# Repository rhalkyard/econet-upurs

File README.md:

# UPURS Dual User Port module for BBC Master Econet Slot

The BBC Master had optional support for Acorn's Econet network. Oddly, all machines had an Econet DIN-5 port populated on the back panel, while the optional hardware to support it was placed on a daughtercard.

This card instead uses the Econet slot to provide a pair of extra user ports, placing a 65C22 VIA at the I/O addresses reserved for the Econet hardware. Additionally, it repurposes the unused Econet port on the back panel for a [UPURS](https://www.retro-kit.co.uk/UPURS/) serial port.

3D rendering of PCB:

Early prototype installed in my BBC Master (excuse the bodge wires, that issue has been resolved)

## Bill of Materials

Reference   | Description
------------|------------
C1          | 0.1 uF ceramic
D1, D2      | 1N4148 (or similar)
J1          | 0.1" pin header, 19x1 pins
J2          | 0.1" pin header, 5x1 pins
J3, J4      | 0.1" pin header, 10x2 pins, shrouded
R1, R2      | 4.7Kohm
U1          | W65C22N VIA, 40 pin DIP

## UPURS

[UPURS](https://www.retro-kit.co.uk/UPURS/) is a fast software-driven RS232 interface, commonly used for exchanging data with modern PCs.

By populating R1, R2, D1 and D2, and bridging JP1 and JP2, the otherwise-unused Econet port can be connected to a serial port for use with UPURS by wiring a cable as follows:

Signal | 180° 5-pin DIN plug  | DE-9 socket
-------|----------------------|-------------
TXD    | 1                    | 3
CTS    | 4                    | 8
Ground | 2                    | 5
RTS    | 5                    | 7
RXD    | 3                    | 2

(note that pins on the DIN plug are numbered as follows, looking at the back of the computer):

```

1           3
   4     5
      2
```

A version of the UPURS software, modified to support this hardware configuration can be found in [this StarDot.co.uk thread](https://stardot.org.uk/forums/viewtopic.php?p=73960&sid=e43f65395b8c5ee131d509cb647cd489#p73960).

## Software Compatibility

In order to use the extra user ports, software must be modified to communicate with the new VIA at `&FEA0` instead of the User VIA at `&FE60`. If only the VIA base address is converted, software will use Port B. To use Port A, software will need to be modified to use `&FEA1` as the port register, and `&FEA3` as the data-direction register. If the synchronous serial port or handshaking functions are to be used with Port A, then further modifications will need to be made.

### Interrupts

The only interrupt line available on the Econet slot is NMI. By default, the VIA's interrupt output is left disconnected, as handling NMIs correctly under MOS is somewhat complicated.

If you want to be able to generate interrupts, bridge jumper J3 to connect the VIA's interrupt output to NMI. Software that wishes to use NMIs must issue appropriate service calls to claim and release the NMI handler area at `&D00`, install their own handler code there, and accept incoming service call requests to release the handler.

### Timing

The Econet slot is clocked off the 'raw' Phi2 CPU clock, rather than the 1MHz clock of the user VIA. This may cause timing complications:

* Reads and writes will occur at 2MHz, which may throw off timing-sensitive bit-banging.

* Timers will count inconsistently - at 2MHz during RAM and ROM accesses, but 1MHz during most I/O accesses.

#### Modifying timing-critical code

From the perspective of the 2MHz clock, access to devices on the 1MHz bus causes the processor to 'lose' two cycles - this is illustrated on Page 443 of the [BBC Microcomputer Advanced User Guide](https://stardot.org.uk/mirrors/www.bbcdocs.com/filebase/essentials/BBC%20Microcomputer%20Advanced%20User%20Guide.pdf). Conveniently, this is the same number of cycles as the `NOP` instruction, so adding either one or two `NOP`s (depending on the instruction) for each time-critical access should be enough to keep timing consistent with a 1MHz VIA.

For absolute addressing, the following rule of thumb applies:

* 4-cycle instructions (`LDA`, `ADC`, `AND`, `ORA` etc.) have 1 memory access, and thus will lose 2 cycles and require one `NOP`.

* 6-cycle instructions (`ASL`, `LSR`, `ROL`, `ROR`, `INC`, `DEC`) have two memory accesses, and thus will lose 4 cycles and require two `NOP`s.

In general, putting the `NOP`(s) before the instruction in question should provide the closest approximation to the 1MHz timing, but that may vary based on

## Econet Slot Information

If you want to build your own hardware to fit the Master's Econet slot, this information might be of use:

The Econet slot provides 16 addresses from `&FEA0`-`&FEAF`, accessed at the full 2MHz CPU speed. The `/NMI` interrupt line is exposed as `/NETINT` and suitable for either TTL or open-collctor outputs, but `/IRQ` is not available.

### Pinouts

#### SK5 (Econet Module bus connector)

SK5 is a 1x19 socket with 0.1" pin spacings, suitable for regular square-pin headers.

For some reason, the pins are numbered A, B, 1..17, instead of 1..19.

Pins are numbered from left to right, when viewing the computer from the front.

Pin   | Signal
------|-------
A     | A3
B     | A2
1     | /NETINT (gets ORed into /NMI by IC15)
2     | R/W
3     | /ADLC (select line for addresses `&FEA0`-`&FEAF`, generated by IC15)
4     | Phi2 (2 MHz clock)
5     | A0
6     | A1
7-14  | D0-D7
15    | /RESET
16    | 0V
17    | +5V

Note that the Econet slot is not on the 1MHz bus - Phi2 is the 'raw' CPU clock, connected to the same net as the processor. As well as the faster access speed, this also means that the clock will be stretched to 1MHz during 1MHz bus accesses. This will cause issues with devices that derive internal clocks from their system-clock input (such as the timers on a VIA).

`/NETINT` goes directly to the IC15 I/O controller (i.e. no wired-OR connections), and has a 2.2K pull-up resistor. This should make it suitable for either open-collector or TTL IRQ outputs.

#### SK6 (Econet module port connector)

SK6 is a 1x5 socket with 0.1" pin spacings, suitable for standard square-pin headers. It connects to the Econet port on the rear of the machine, as follows.

SK6   | Econet port
------|------------
1     | 1
2     | 4
3     | 2 (grounded on main board)
4     | 5
5     | 3

Some machines (non-UK market boards?) may have a common-mode choke array (SIL2) between SK6 and the Econet port.

### Dimensions

Measurement annotations have been added to the PCB layout file in the 'User.Comments' layer.

There is ample space to extend the circuit board to the left, however, space is constrained on all other sides - case edges to the right and rear, and ROM sockets toward the front.

## References

* [StarDot thread on adding an 'Econet User Port'](https://stardot.org.uk/forums/viewtopic.php?f=3&t=7149)

* [Redrawn BBC Master schematics](https://stardot.org.uk/forums/viewtopic.php?t=22660)

* [BBC Master Advanced Reference Manual](https://stardot.org.uk/forums/viewtopic.php?t=21734)

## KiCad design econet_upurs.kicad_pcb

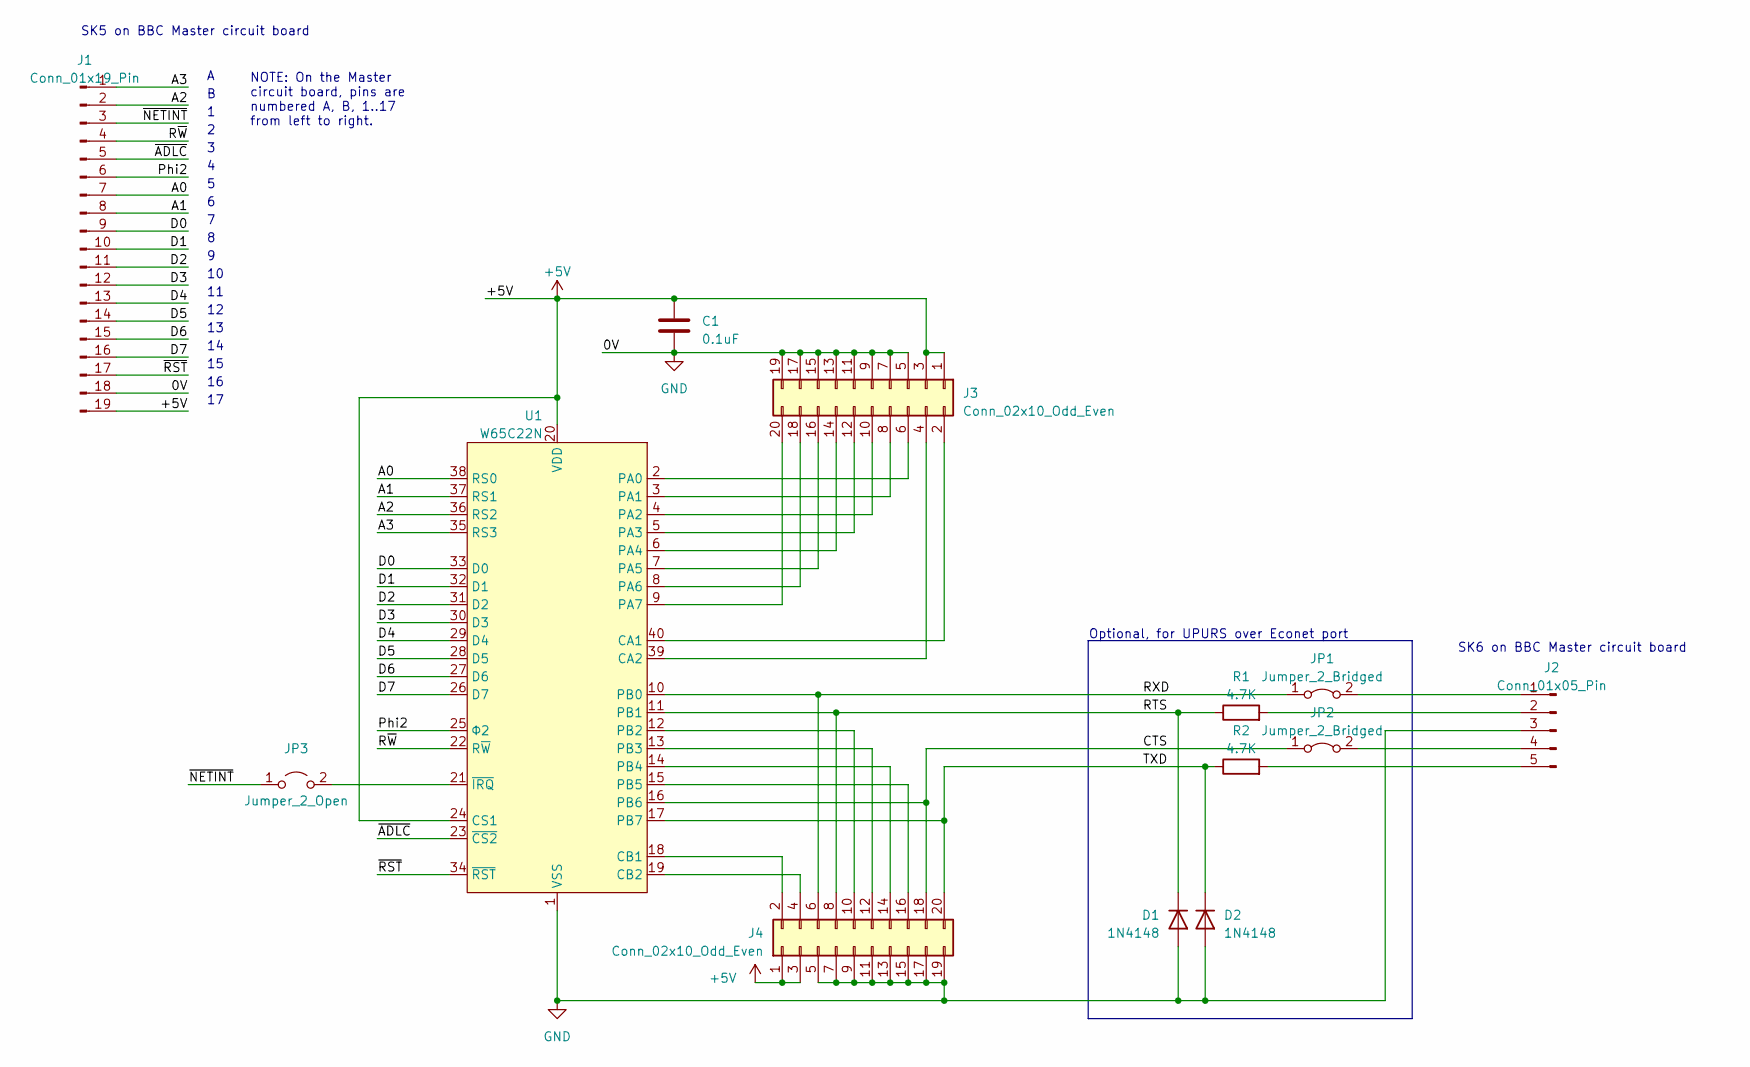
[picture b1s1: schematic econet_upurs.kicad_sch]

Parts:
C1: 0.1uF; C_Disc_D3.0mm_W1.6mm_P2.50mm
D1, D2: 1N4148; D_DO-35_SOD27_P7.62mm_Horizontal
J1: Conn_01x19_Pin; PinHeader_1x19_P2.54mm_Vertical
J2: Conn_01x05_Pin; PinHeader_1x05_P2.54mm_Vertical
J3, J4: Conn_02x10_Odd_Even; IDC-Header_2x10_P2.54mm_Vertical
JP1, JP2: Jumper_2_Bridged; TestPoint_2Pads_Pitch2.54mm_Drill0.8mm
JP3: Jumper_2_Open; PinHeader_1x02_P2.54mm_Vertical
R1, R2: 4.7K; R_Axial_DIN0207_L6.3mm_D2.5mm_P7.62mm_Horizontal
U1: W65C22N; DIP-40_W15.24mm

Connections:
+5V: C1.1, J1.19, J3.1, J3.3, J4.1, J4.3, U1.20 (VDD), U1.24 (CS1)
/A0: J1.7, U1.38 (RS0)
/A1: J1.8, U1.37 (RS1)
/A2: J1.2, U1.36 (RS2)
/A3: J1.1, U1.35 (RS3)
/CTS: J4.18, JP2.1 (A), U1.16 (PB6)
/D0: J1.9, U1.33 (D0)
/D1: J1.10, U1.32 (D1)
/D2: J1.11, U1.31 (D2)
/D3: J1.12, U1.30 (D3)
/D4: J1.13, U1.29 (D4)
/D5: J1.14, U1.28 (D5)
/D6: J1.15, U1.27 (D6)
/D7: J1.16, U1.26 (D7)
/Phi2: J1.6, U1.25 (Φ2)
/RTS: D1.1 (K), J4.8, R1.1, U1.11 (PB1)
/RXD: J4.6, JP1.1 (A), U1.10 (PB0)
/R~W: J1.4, U1.22 (R~W)
/TXD: D2.1 (K), J4.20, R2.1, U1.17 (PB7)
/~ADLC: J1.5, U1.23 (~CS2)
/~NETINT: J1.3, JP3.1 (A)
/~RST: J1.17, U1.34 (~RST)
GND: C1.2, D1.2 (A), D2.2 (A), J1.18, J2.3, J3.5, J3.7, J3.9, J3.11, J3.13, J3.15, J3.17, J3.19, J4.5, J4.7, J4.9, J4.11, J4.13, J4.15, J4.17, J4.19, U1.1 (VSS)
unnamed: J2.1, JP1.2 (B)
unnamed: J2.2, R1.2
unnamed: J2.4, JP2.2 (B)
unnamed: J2.5, R2.2
unnamed: J3.2, U1.40 (CA1)
unnamed: J3.4, U1.39 (CA2)
unnamed: J3.6, U1.2 (PA0)
unnamed: J3.8, U1.3 (PA1)
unnamed: J3.10, U1.4 (PA2)
unnamed: J3.12, U1.5 (PA3)
unnamed: J3.14, U1.6 (PA4)
unnamed: J3.16, U1.7 (PA5)
unnamed: J3.18, U1.8 (PA6)
unnamed: J3.20, U1.9 (PA7)
unnamed: J4.2, U1.18 (CB1)
unnamed: J4.4, U1.19 (CB2)
unnamed: J4.10, U1.12 (PB2)
unnamed: J4.12, U1.13 (PB3)
unnamed: J4.14, U1.14 (PB4)
unnamed: J4.16, U1.15 (PB5)
unnamed: JP3.2 (B), U1.21 (~IRQ)

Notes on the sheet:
NOTE: On the Master circuit board, pins are numbered A, B, 1..17 from left to right.
SK5 on BBC Master circuit board
SK6 on BBC Master circuit board
Optional, for UPURS over Econet port

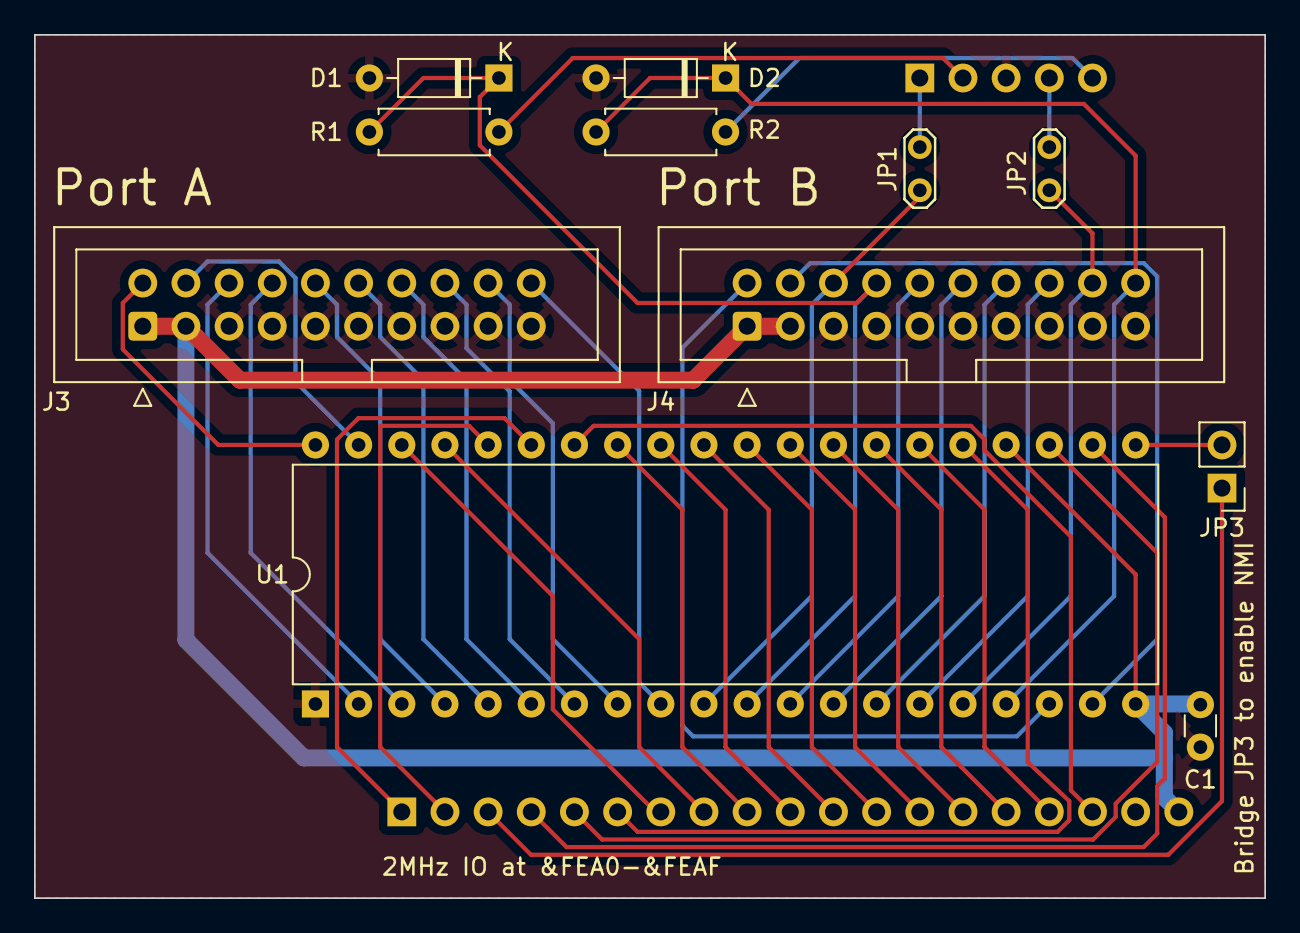
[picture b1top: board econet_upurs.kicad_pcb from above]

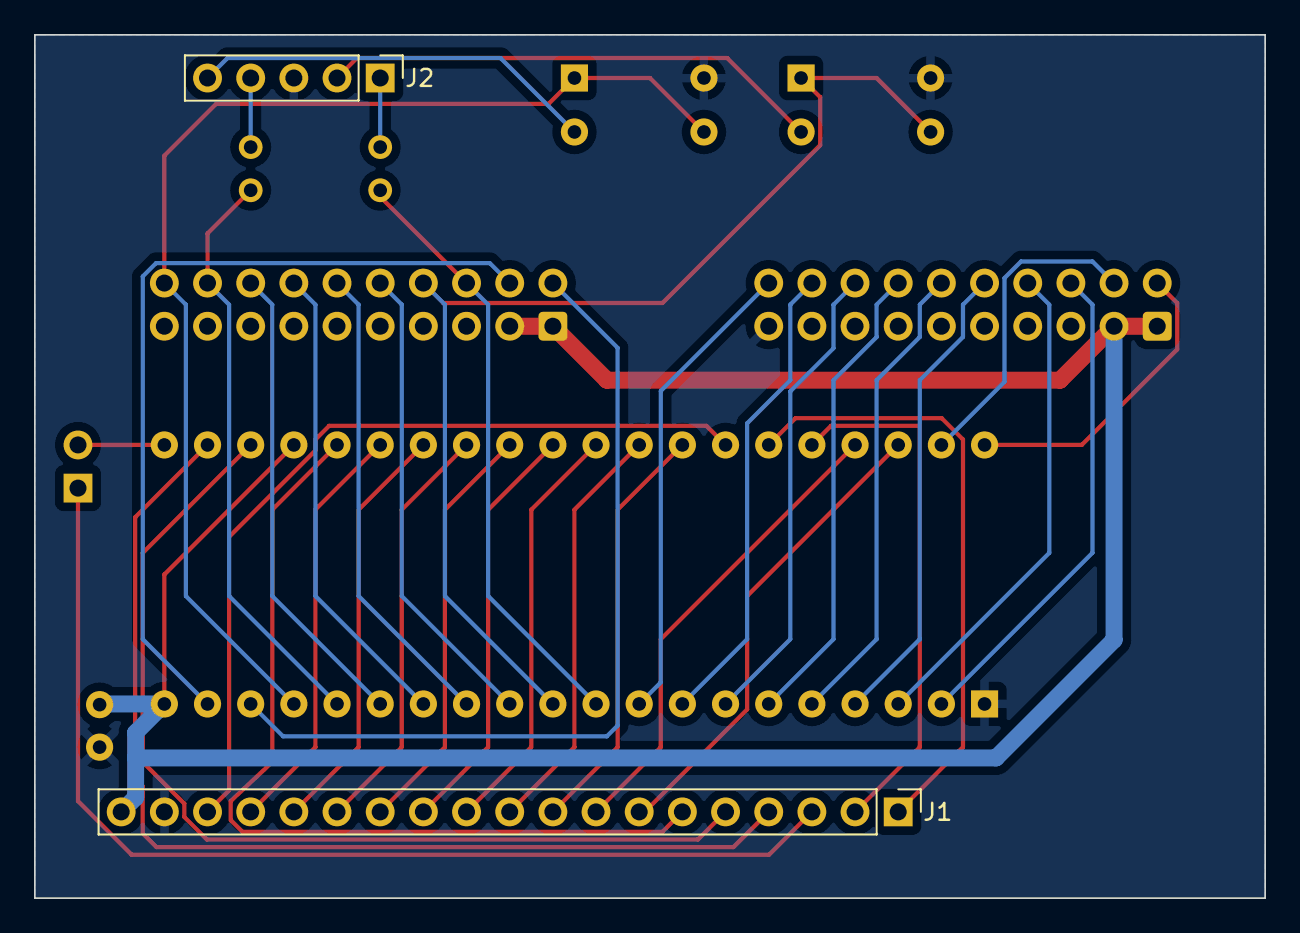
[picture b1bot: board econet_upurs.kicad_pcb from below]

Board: 2 copper layers, 72.4 x 50.8 mm, 13 parts (2 on the bottom side), 44 nets.

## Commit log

2023-03-13 Add notes on timing modifications
